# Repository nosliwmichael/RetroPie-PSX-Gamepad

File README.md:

# RetroPie-PSX-Gamepad
A Python script for reading button and joystick values in the Linux User-Space and translating them into inputs for a virtual gamepad.

This project was designed for a handheld RetroPie setup which uses an MCP3008 to handle Analog to Digital conversion and an MCP23017 for GPIO Expansion. The two chips combined can handle a total of 24 inputs (8 for the MCP3008 and 16 for the MCP23017). This does not include any available GPIO pins on the Raspberry Pi itself. There is support for adding button mappings through the native GPIO pins via the gamepad.json file but that is left up to the user.

**Note:** If you set the RP_PSX_GP_LOG environment variable equal to `DEBUG`, the script will print the values of whatever input device was pressed. This is useful for identifying mapping issues or seeing if your input is being registered at all. Additionally, this will also print the PORT values of the MCP23017 which can be useful for identifying which bits are on or off.

# Documentation
### Datasheets
- [MCP3008 Datasheet](https://ww1.microchip.com/downloads/aemDocuments/documents/MSLD/ProductDocuments/DataSheets/MCP3004-MCP3008-Data-Sheet-DS20001295.pdf)
- [MCP23017 Datasheet](https://ww1.microchip.com/downloads/en/devicedoc/20001952c.pdf)
### Tutorials
Tutorial for using an MCP3008 with Joysticks on a Raspberry Pi:
- [How to use a Joystick on the Raspberry Pi (with an MCP3008)](https://tutorials-raspberrypi.com/raspberry-pi-joystick-with-mcp3008/)

Tutorial for using an MCP23017 with a Raspberry Pi:
- [How to use an MCP23017 I2C with a Raspberry Pi Pt. 1](https://www.raspberrypi-spy.co.uk/2013/07/how-to-use-a-mcp23017-i2c-port-expander-with-the-raspberry-pi-part-1/)
- [How to use an MCP23017 I2C with a Raspberry Pi Pt. 2](https://www.raspberrypi-spy.co.uk/2013/07/how-to-use-a-mcp23017-i2c-port-expander-with-the-raspberry-pi-part-2/)
- [How to use an MCP23017 I2C with a Raspberry Pi Pt. 3](https://www.raspberrypi-spy.co.uk/2013/07/how-to-use-a-mcp23017-i2c-port-expander-with-the-raspberry-pi-part-3/)

# Requirements
* Hardware
  * Raspberry Pi 3/4
  * MCP3008
  * MCP23017
  * Push buttons
  * Joysticks
  * Wiring, Breadboards, etc.
* Software
  * Enable SPI in Raspberry Pi configurations
    * `sudo raspi-config` > Options > Enable SPI
  * Enable I2C in Raspberry Pi configurations
    * `sudo raspi-config` > Options > Enable I2C
  * Load uinput Kernel Module
    * `modprobe uinput`
  * Python3
    * `sudo apt install python3`
  * PIP3
    * `sudo apt install pip3`

# Software Installation
### Steps
1. Update / Upgrade
    * `sudo apt update`
    * `sudo apt upgrade`
2. Clone this repository onto your RetroPie device.
    * `git clone https://github.com/nosliwmichael/RetroPie-PSX-Gamepad.git`
3. Install python-uinput
    * `sudo pip3 install python-uinput`
4. Install smbus2
    * `sudo pip3 install smbus2`
5. Update gamepad.json with correct GPIO/PIN/Channel mappings
    * `vim ./RetroPie-PSX-Gamepad/gamepad.json`
6. Test that the script works
    * `sudo python3 ./RetroPie-PSX-Gamepad/src`
7. Setup the script to run as a systemd service so that it starts up on boot.

# Gamepad Configuration
Input mappings for the gamepad can be configured with the gamepad.json file.
Refer to the the python-uinput source code for event code mappings:
https://github.com/tuomasjjrasanen/python-uinput/blob/master/src/ev.py \
The example below should be suitable in most cases unless you are looking to add/remove functionality.\
### gamepad.json
#### Main properties
|Property|Description|
|--------|-----------|
|DEVICE_NAME|This is the name of your controller. It can be set to whatever you want and will be picked up by RetroPie to identify the gamepad. If you change this name after you've configured your input in RetroPie, it may not recognize your gamepad and ask you to reconfigure the input.|
|VENDOR|A vendor ID. Again, this can be set to anything, it's the ID of the maker. Similary to above, if you change this value after you've configured your input in RetroPie, it may not recognize your gamepad and ask you to reconfigure the input.|
|PRODUCT|A product ID. This can also be set to anything, it's the ID of the controller. Similary to above, if you change this value after you've configured your input in RetroPie, it may not recognize your gamepad and ask you to reconfigure the input.|
|GPIO|This array let's you configure inputs connected directly to the Raspberry Pi.|
|MCP3008|This array let's you configure inputs connected to the MCP3008.|
|MCP23017|This array let's you configure inputs connected to the MCP23017.|

#### Event Properties
|Property|Description|
|--------|-----------|
|name|This is the name of the input. You can call this whatever you like. I named mine after their respective [Linux Input Events](https://www.kernel.org/doc/html/latest/input/gamepad.html). The main purpose here was to help with debugging.|
|event_code|Since this project uses python-uinput to map your inputs to a virtual gamepad, these event codes need to match the ones in this file for whichever event you're trying to trigger. [python-uinput/src/ev.py](https://github.com/tuomasjjrasanen/python-uinput/blob/master/src/ev.py). My understanding is that the first value in the tuple represents the type of input [BTN (0x01), REL (0x02), ABS(0x03)] and the second value is the actual linux event code. The ABS ones might look confusing in the gamepad.json file because they have four extra numbers in their tuple. This is strictly for joysticks where the extra values are MIN, MAX, FUZZ and FLAT. |
|pin|This is the GPIO or Pin number on the chip that you connected the input to. For the MCP3008, this is going to correspond to the channel.|
|port|This is only relevant to the MCP23017 to help distinguish which port (A or B) the input is on.|
|is_digital|This is a boolean to help determine the type of input. If analog, this value should be false. Analog values have their own special event handling.|

#### Example of the gamepad.json configurations:
```json
{
    "DEVICE_NAME": "RetroPie-PSX-Gamepad",
    "VENDOR": 6969,
    "PRODUCT": 420,
    "GPIO" : [
    ],
    "MCP3008" : [
        { "name": "BTN_THUMBL", "event_code": "(0x01, 0x13d)", "pin": 0, "port": null, "is_digital": true },
        { "name": "ABS_X", "event_code": "(0x03, 0x00, 0, 1023, 50, 0)", "pin": 1, "port": null, "is_digital": false },
        { "name": "ABS_Y", "event_code": "(0x03, 0x02, 0, 1023, 50, 0)", "pin": 2, "port": null, "is_digital": false },
        { "name": "BTN_THUMBR", "event_code": "(0x01, 0x13e)", "pin": 5, "port": null, "is_digital": true },
        { "name": "ABS_RX", "event_code": "(0x03, 0x03, 0, 1023, 50, 0)", "pin": 6, "port": null, "is_digital": false },
        { "name": "ABS_RY", "event_code": "(0x03, 0x04, 0, 1023, 50, 0)", "pin": 7, "port": null, "is_digital": false }
    ],
    "MCP23017" : [
        { "name": "BTN_MODE", "event_code": "(0x01, 0x13c)", "pin": 7, "port": "A", "is_digital": true },
        { "name": "BTN_START", "event_code": "(0x01, 0x13b)", "pin": 6, "port": "A", "is_digital": true },
        { "name": "BTN_SELECT", "event_code": "(0x01, 0x13a)", "pin": 5, "port": "A", "is_digital": true },
        { "name": "BTN_TL", "event_code": "(0x01, 0x136)", "pin": 4, "port": "A", "is_digital": true },
        { "name": "BTN_TR", "event_code": "(0x01, 0x137)", "pin": 3, "port": "A", "is_digital": true },
        { "name": "BTN_TL2", "event_code": "(0x01, 0x138)", "pin": 2, "port": "A", "is_digital": true },
        { "name": "BTN_TR2", "event_code": "(0x01, 0x139)", "pin": 1, "port": "A", "is_digital": true },

        { "name": "BTN_DPAD_LEFT", "event_code": "(0x01, 0x222)", "pin": 7, "port": "B", "is_digital": true },
        { "name": "BTN_DPAD_UP", "event_code": "(0x01, 0x220)", "pin": 6, "port": "B", "is_digital": true },
        { "name": "BTN_DPAD_RIGHT", "event_code": "(0x01, 0x223)", "pin": 5, "port": "B", "is_digital": true },
        { "name": "BTN_DPAD_DOWN", "event_code": "(0x01, 0x221)", "pin": 4, "port": "B", "is_digital": true },
        { "name": "BTN_SOUTH", "event_code": "(0x01, 0x130)", "pin": 3, "port": "B", "is_digital": true },
        { "name": "BTN_WEST", "event_code": "(0x01, 0x134)", "pin": 2, "port": "B", "is_digital": true },
        { "name": "BTN_NORTH", "event_code": "(0x01, 0x133)", "pin": 1, "port": "B", "is_digital": true },
        { "name": "BTN_EAST", "event_code": "(0x01, 0x131)", "pin": 0, "port": "B", "is_digital": true }
    ]
}
```

# Wiring
The following is a diagram of the MCP3008. This chip is responsible for converting analog signals, such as a joystick, into digital signals that are compatible with the Raspberry Pi. It uses the SPI interface for communication with the Raspberry Pi and it supports up to 8 channels. Since the MCP3008 channels output a 10 bit signal, this means the value could range between 0 (0000000000) and 1023 (1111111111).\
Additionally, a single joystick can output 3 signals; X-Axis (Analog), Y-Axis (Analog), Click (Digital). The chip's input channels can also receive digital signals like from the joystick's button click; the output would be either 0 or 1023. In my diagrams, I chose to use one channel for each of my joystick's buttons. However, if I were to need more channels for additional analog inputs, like for my left and right triggers or a volume knob, I will need to reassign the joystick buttons to an available GPIO on the MCP23017 or the Raspberry Pi.\
Keep in mind, if you choose to use the MCP3008 for push buttons, you should make use of pull up resistors because the MCP3008 does not have any internal pull up resistors of its own.

The following is a diagram of the MCP23017. This chip is a simple GPIO port expander which allows us to attach more devices to the Raspberry Pi by leveraging its I2C interface. There is an SPI variation of this chip if you feel that the two wire I2C interface is too slow. For simple button inputs, I think it works just fine.\
The three address pins (A0, A1, A2) are used to assign the chip an address by pulling each of the HIGH or LOW. In my configuration, I've wired each address to Ground (LOW), which means the address of my MCP23017 is 0x20 (32).\
Fortunately, the MCP23017 has internal pull up resistors for each of the GPIO ports (GPA / GPB) which I've enabled in the python scrip by default. Therefore, it is not necessary to wire up any external pull up resistors for your buttons/switches.\
The chip also has two pins for enabling interrupts. In theory, this could be used to allow the MCP23017 to inform the Raspberry Pi that a button press/depress occurred, rather than the Raspberry Pi polling the chip every 0.05 seconds. This would be more efficient in terms of CPU usage. However, because my use case uses an MCP3008, which does not support interrupts, I needed to implement a polling mechanism anyway. With that in mind I decided it wasn't worth supporting interrupt behavior at this time. In the future I could update the code to use interrupts if only the MCP23017 is in use and not the Pi's GPIO or the MCP3008.

In this diagram, I wanted to give you an idea of how each of the components could be configured to work with this gamepad driver. You can see all of the D-Pad and Action buttons are wired up to the B port pins on the MCP23017. The left/right shoulder/trigger buttons as well as the start, select, and home (hotkey) buttons are all wired up to the A port. There are still two open pins on port A which could be used for a power button or whatever you want.\
The small raspberry icons are there to tell you how each pin of the MCP3008/MCP23017 map to their corresponding GPIO pin on the Raspberry Pi.

Finally, this is an example of the entire thing connected with a combination of wire and jumper cables. My Raspberry Pi is attached to a [CanaKit Raspberry Pi GPIO Breakout Board](https://www.canakit.com/raspberry-pi-gpio-breakout.html) to make it easier to wire the ICs to the correct GPIO pin. If you boot up RetroPie with the script and this controller configuration, it should detect your gamepad and allow you to configure your inputs. Once you've confirmed it works, the final step would be to move this setup to something more official, like a perfboard or a custom PCB.

# Custom PCB
Using software like KiCAD, we can draw up a schematic with what we've learned on our breadboard. We can use the built in library to select the components we want or design our own symbols/footprints for those that don't have them. With that out of the way, we can make a board file out of the schematic and lay things out the way we want them. The final step is to generate the files the manufacturer will need to create the board for us.

Check out the [PCB-Files](https://github.com/nosliwmichael/RetroPie-PSX-Gamepad/tree/PCB-Files) branch if you want to make your own.

# Prototype
Checkout the [Case-3D-Model](https://github.com/nosliwmichael/RetroPie-PSX-Gamepad/tree/Case-3D-Model) branch if you want to make your own.

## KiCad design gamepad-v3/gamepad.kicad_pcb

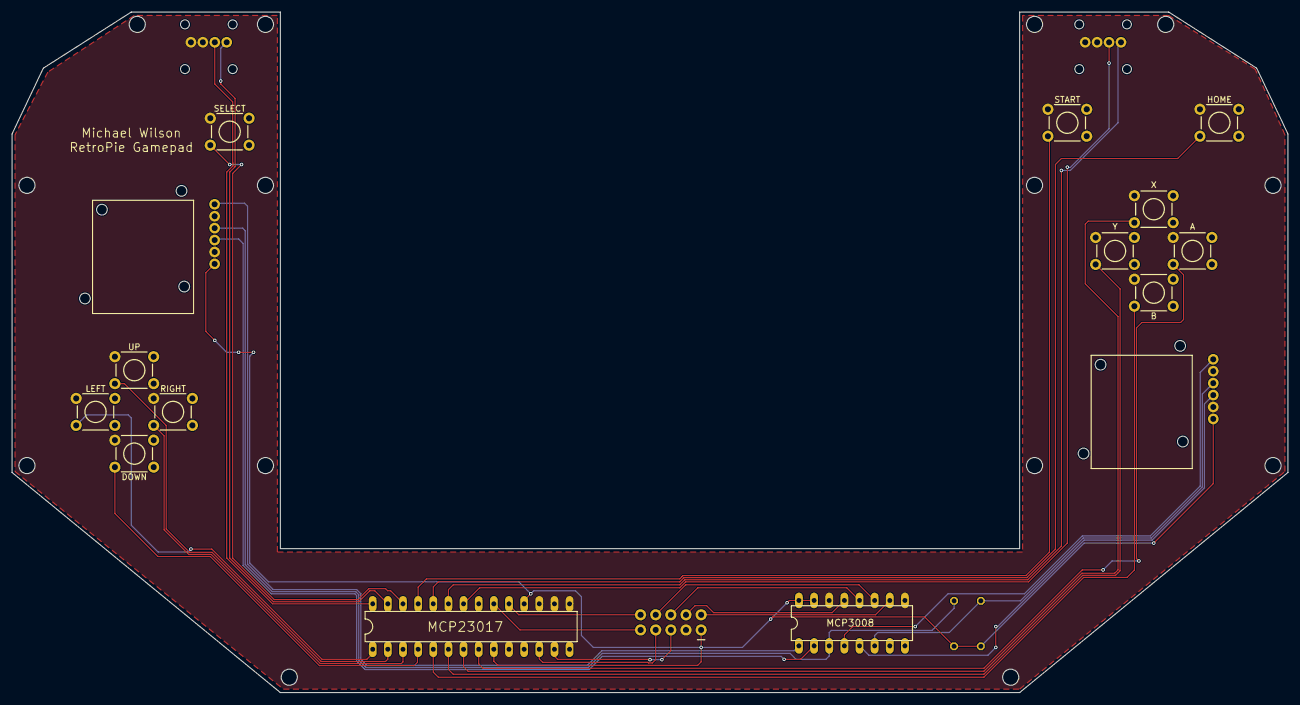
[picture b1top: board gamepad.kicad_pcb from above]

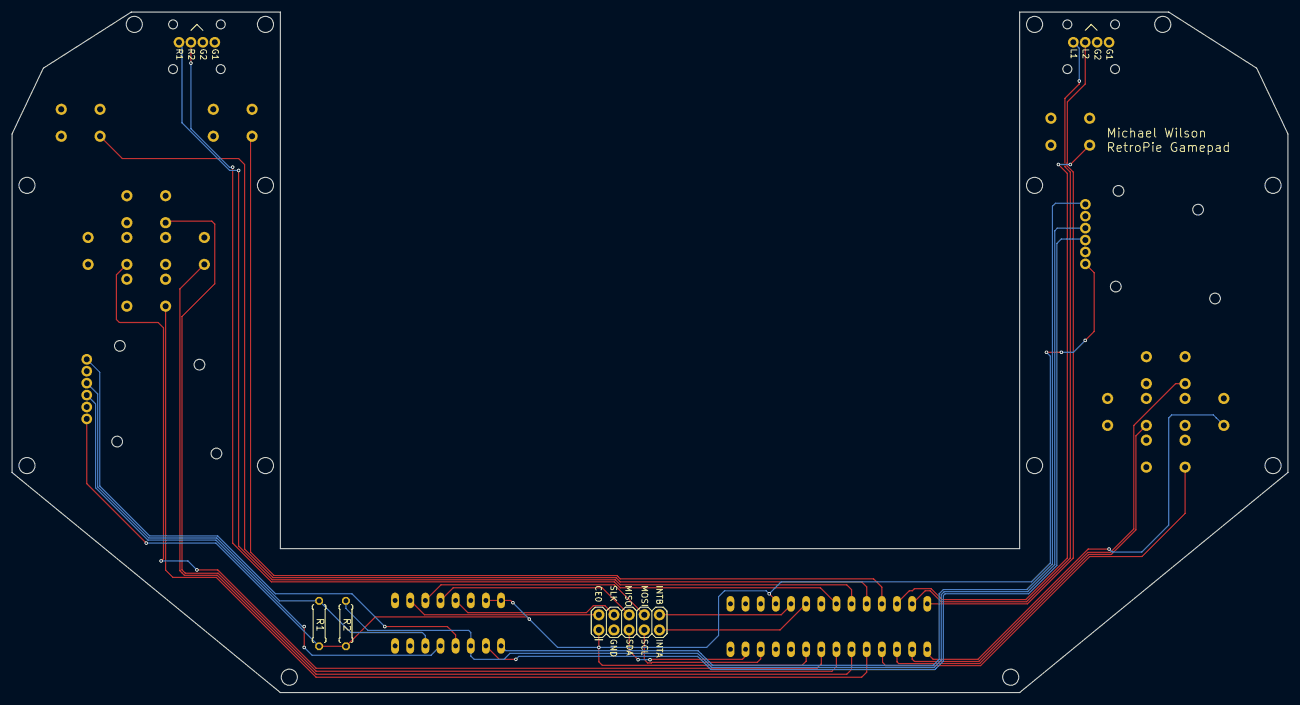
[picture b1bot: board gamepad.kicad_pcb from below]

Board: 2 copper layers, 214.0 x 114.1 mm, 20 parts (5 on the bottom side), 31 nets.

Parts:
A: MOMENTARY-SWITCH-SPST-PTH-6.0MM; TACTILE_SWITCH_PTH_6.0MM_535
B: MOMENTARY-SWITCH-SPST-PTH-6.0MM; TACTILE_SWITCH_PTH_6.0MM_535
DOWN: MOMENTARY-SWITCH-SPST-PTH-6.0MM; TACTILE_SWITCH_PTH_6.0MM_535
HOME: MOMENTARY-SWITCH-SPST-PTH-6.0MM; TACTILE_SWITCH_PTH_6.0MM_535
IC1: MCP23017; DIL28-3_420
IC2: MCP3008; DIL16_420
J1: 2X5_513
LEFT: MOMENTARY-SWITCH-SPST-PTH-6.0MM; TACTILE_SWITCH_PTH_6.0MM_535
LEFT_STICK0: 5628
LEFT_TRIGGERS0: MJTP2205
R1, R2: 0207_7_348
RIGHT: MOMENTARY-SWITCH-SPST-PTH-6.0MM; TACTILE_SWITCH_PTH_6.0MM_535
RIGHT_STICK0: 5628
RIGHT_TRIGGERS0: MJTP2205
SELECT: MOMENTARY-SWITCH-SPST-PTH-6.0MM; TACTILE_SWITCH_PTH_6.0MM_535
START: MOMENTARY-SWITCH-SPST-PTH-6.0MM; TACTILE_SWITCH_PTH_6.0MM_535
UP: MOMENTARY-SWITCH-SPST-PTH-6.0MM; TACTILE_SWITCH_PTH_6.0MM_535
X: MOMENTARY-SWITCH-SPST-PTH-6.0MM; TACTILE_SWITCH_PTH_6.0MM_535
Y: MOMENTARY-SWITCH-SPST-PTH-6.0MM; TACTILE_SWITCH_PTH_6.0MM_535

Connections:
GND: A.1, B.1, DOWN.1, HOME.1, IC1.10, IC1.15, IC1.16, IC1.17, IC2.9, IC2.14, J1.3, LEFT.1, LEFT_STICK0.GND1, LEFT_STICK0.GND2, LEFT_TRIGGERS0.GND$1, LEFT_TRIGGERS0.GND$2, RIGHT.1, RIGHT_STICK0.GND1, RIGHT_STICK0.GND2, RIGHT_TRIGGERS0.GND$1, RIGHT_TRIGGERS0.GND$2, SELECT.1, START.1, UP.1, X.1, Y.1
MCP3008_CH0: IC2.1, LEFT_STICK0.AD1
MCP3008_CH1: IC2.2, LEFT_STICK0.AD2
MCP3008_CH2: IC2.3, LEFT_STICK0.SW, R2.1
MCP3008_CH3: IC2.4, RIGHT_STICK0.AD1
MCP3008_CH4: IC2.5, RIGHT_STICK0.AD2
MCP3008_CH5: IC2.6, R1.1, RIGHT_STICK0.SW
MCP23017_GPA1: IC1.22, RIGHT_TRIGGERS0.IN$2
MCP23017_GPA2: IC1.23, RIGHT_TRIGGERS0.IN$1
MCP23017_GPA3: HOME.3, IC1.24
MCP23017_GPA4: IC1.25, START.3
MCP23017_GPA5: IC1.26, SELECT.3
MCP23017_GPA6: IC1.27, LEFT_TRIGGERS0.IN$1
MCP23017_GPA7: IC1.28, LEFT_TRIGGERS0.IN$2
MCP23017_GPB0: IC1.1, LEFT.3
MCP23017_GPB1: IC1.2, UP.3
MCP23017_GPB2: IC1.3, RIGHT.3
MCP23017_GPB3: DOWN.3, IC1.4
MCP23017_GPB4: B.3, IC1.5
MCP23017_GPB5: IC1.6, Y.3
MCP23017_GPB6: IC1.7, X.3
MCP23017_GPB7: A.3, IC1.8
PI_CE0: IC2.10, J1.2
PI_INTA: IC1.20, J1.9
PI_INTB: IC1.19, J1.10
PI_MISO: IC2.12, J1.6
PI_MOSI: IC2.11, J1.8
PI_SCL: IC1.12, J1.7
PI_SDA: IC1.13, J1.5
PI_SLK: IC2.13, J1.4
VCC: IC1.9, IC1.18, IC2.15, IC2.16, J1.1, LEFT_STICK0.VCC, R1.2, R2.2, RIGHT_STICK0.VCC

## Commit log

2024-01-28 Setup general idea for testing
2024-01-29 Add more gamepad buttons and extract some of the code into a separate file.
2024-01-29 Fix gamepadValues tuple
2024-01-29 Slight fixes to event mapping
2024-01-29 Fix btn mapping
2024-01-29 Add more button functionality
2024-01-31 Fix convertDigitalBtnValue method
2024-01-31 Only emit if values changed
2024-01-31 Change thumb buttons to emit. Only synchronize at the end
2024-01-31 Add a configuration file for various gamepad inputs. It should support GPIO pins, MC3008 channels and MCP23017 channels.
2024-01-31 Attempt to construct gamepad.cfg path relative the script's location.
2024-01-31 Push fix for ButtonMap
2024-01-31 Read configs as integer instead of string
2024-02-01 Refactor to be a bit more object oriented. Allow for external pin configuration
2024-02-01 Remove unused files
2024-02-01 Update old code
2024-02-01 Add args to eventHandler
2024-02-01 Increase delay and add logging to help with testing
2024-02-01 Try to fix logging
2024-02-01 Try to fix logging again
2024-02-01 Try to fix logging again x2
2024-02-01 Add logging to Events
2024-02-01 Convert event_codes from hex to decimal
2024-02-01 Remove extra analog logic
2024-02-01 Revert event_codes back to hex
2024-02-01 Try implementing weird tuples in gamepad config
2024-02-01 Revert tuples
2024-02-01 Try using a dictionary to pull event codes dynamically
2024-02-01 Separate weird tuple stuff from dict
2024-02-01 Add back analog event logic
2024-02-01 Add log for debugging
2024-02-01 Prevent digital from going analog
2024-02-01 Just make analog update all the time
2024-02-01 Move log
2024-02-01 Reduce delay
2024-02-01 Remove logs
2024-02-03 Add support for MCP23017
2024-02-03 Fix issues with MCP23017 implementation
2024-02-03 Put fix in wrong place
2024-02-03 Fix KeyError with event_map
2024-02-03 Add BTN_MODE event for hotkey
2024-02-03 Fix B port pins
2024-02-03 Add BTN_TR2 to port b
2024-02-03 Fix correct address
2024-02-04 Move action buttons to the MCP23017
2024-02-05 Refactor code to clean up event loops and MCP23017 reads
2024-02-05 Modify multi with statement to be compatable with older versions of python3
2024-02-05 Move spi speed after spi open
2024-02-05 Remove self param from functions outside of a class definition
2024-02-05 Fix MCP3008 __enter__ method
2024-02-05 Refactor (#1)
    * Refactor to be a bit more object oriented. Allow for external pin configuration
    * Remove unused files
    * Update old code
    * Add args to eventHandler
    * Increase delay and add logging to help with testing
    * Try to fix logging
2024-02-05 Print gamepad_map for debugging
2024-02-05 Call printGamepadmap
2024-02-05 Add print statement to MCP23017 init method
2024-02-05 SMBus byte conversion was dropping a bit. We also needed to convert to a list of int.
2024-02-05 Add more debugging logs
2024-02-05 Flip MCP23017 mappings
2024-02-05 Remove logging
2024-02-05 Attempt to make use of the event_code property on the GamepadInput
2024-02-05 Truncate event tuples
2024-02-05 Fix getEvents()
2024-02-05 Update device name and add documentation
2024-02-05 Organizing files
2024-02-05 Additional refactoring (#2)
    * Print gamepad_map for debugging
    * Call printGamepadmap
    * Add print statement to MCP23017 init method
    * SMBus byte conversion was dropping a bit. We also needed to convert to a list of int.
    * Add more debugging logs
    * Flip MCP23017 mappings
2024-02-05 Allow controller info to be configurable.
2024-02-06 Add a cleaner lookout at the breadboard layout
2024-02-06 Add chip diagrams
2024-02-06 Rename breadboard-setupjpg.jpg to breadboard-setup.jpg
2024-02-06 Add updated MCP3008 pin layout
2024-02-06 Add updated pin layout diagram
2024-02-06 Try uploading MCP3008 pin layout
2024-02-06 Update documentation
2024-02-06 Update Documentation (#3)
    * Add chip diagrams
    * Rename breadboard-setupjpg.jpg to breadboard-setup.jpg
    * Update Documentation
2024-02-07 Update README.md and diagrams
2024-02-07 Provide more detailed descriptions and guidance.
2024-02-07 Update README.md and diagrams (#4)
    * Update README.md and diagrams
    * Provide more detailed descriptions and guidance.
    * Provide more detailed descriptions and guidance.
2024-02-07 Rename channel property to pin since it's more generic.
2024-02-07 Allow users to enable print statements for debugging.
2024-02-07 Feature (#5)
    * Rename channel property to pin since it's more generic.
    * Allow users to enable print statements for debugging.
2024-03-12 Upload gamepad mapping for PCB
2024-03-12 Fix gamepad configuration pin values
2025-03-02 Add FreeCAD file for the case
2025-03-02 Rename case.FCStd to 3D-model/case.FCStd
2025-03-02 Create placeholder
2025-03-02 Add more images and documentation for final steps to the project.
2025-03-12 Update case model
